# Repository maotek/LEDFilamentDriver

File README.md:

## LED Filament Driver

---

## Remarks

- KiCad project also contains a driver for EDP displays, however this schematic was not included in the final production PCB.
- Produced by JLCPCB.
- Crystal is not necessary for application not requiring precise timing.

---
## Issues

- Unfortunately, output 9 and 10 do not have PWM output. Will be fixed in the next revisions if any.
- AMS1117 3.3 is rated for 1A, make sure the LED filaments do no consume more than 1A. Otherwise they will overheat.
- For loads higher than 1A, consider buck converters.

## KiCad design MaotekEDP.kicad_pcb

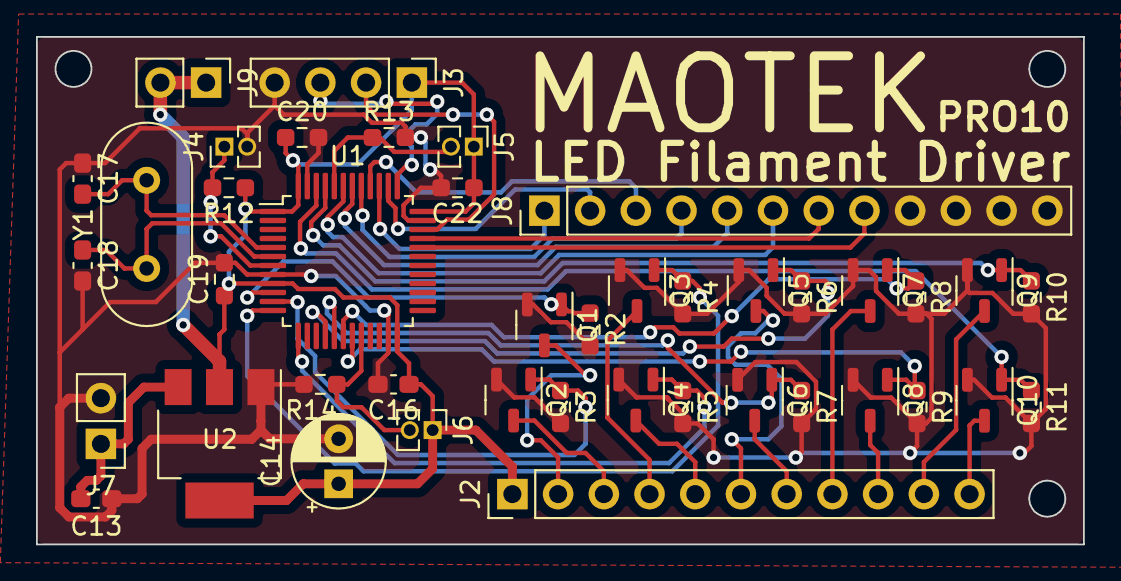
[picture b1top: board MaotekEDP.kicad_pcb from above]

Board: 2 copper layers, 58.2 x 28.2 mm, 42 parts (0 on the bottom side), 38 nets.

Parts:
C13, C16: 100nF; C_0603_1608Metric_Pad1.08x0.95mm_HandSolder
C14: 470uF; CP_Radial_D5.0mm_P2.50mm
C17, C18: 20p; C_0603_1608Metric_Pad1.08x0.95mm_HandSolder
C19, C20, C22: 100nF; R_0603_1608Metric_Pad0.98x0.95mm_HandSolder
J2: Conn_01x11; PinHeader_1x11_P2.54mm_Vertical
J3: Conn_01x04; PinHeader_1x04_P2.54mm_Vertical
J4, J5, J6: Conn_01x02; PinHeader_1x02_P1.27mm_Vertical
J7, J9: Conn_01x02; PinHeader_1x02_P2.54mm_Vertical
J8: Conn_01x12; PinHeader_1x12_P2.54mm_Vertical
Q1, Q2, Q3, Q4, Q5, Q6, Q7, Q8, Q9, Q10: Q_NMOS_GSD; SOT-23-3
R2, R3, R4, R5, R6, R7, R8, R9, R10, R11, R12, R13, R14: 10K; R_0603_1608Metric_Pad0.98x0.95mm_HandSolder
U1: STM32F103C8Tx; LQFP-48_7x7mm_P0.5mm
U2: AMS1117-3.3; SOT-223-3_TabPin2
Y1: 8MHz; Crystal_HC18-U_Vertical

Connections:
32: J8.8, U1.32 (PA11)
33: J8.7, U1.33 (PA12)
38: J8.2, U1.38 (PA15)
39: J8.1, U1.39 (PB3)
40: J8.3, U1.40 (PB4)
41: J8.4, U1.41 (PB5)
42: J8.5, U1.42 (PB6)
43: J8.6, U1.43 (PB7)
+3.3V: C14.1, C16.1, C19.1, C20.1, C22.1, J2.1, J3.1, J5.1, J6.1, J9.1, J9.2, R12.1, U1.1 (VBAT), U1.9 (VDDA), U1.24 (VDD), U1.36 (VDD), U1.48 (VDD), U2.2 (VO)
+5V: C13.1, J7.1, U2.3 (VI)
BOOT0: J5.2, R13.1, U1.44 (BOOT0)
BOOT1: J6.2, R14.1, U1.20 (PB2)
GND: C13.2, C14.2, C16.2, C17.1, C18.2, C19.2, C20.2, C22.2, J3.4, J4.2, J7.2, J8.9, J8.10, J8.11, J8.12, Q1.2 (S), Q2.2 (S), Q3.2 (S), Q4.2 (S), Q5.2 (S), Q6.2 (S), Q7.2 (S), Q8.2 (S), Q9.2 (S), Q10.2 (S), R2.2, R3.2, R4.2, R5.2, R6.2, R7.2, R8.2, R9.2, R10.2, R11.2, R13.2, R14.2, U1.8 (VSSA), U1.23 (VSS), U1.35 (VSS), U1.47 (VSS), U2.1 (GND)
NRST: J4.1, R12.2, U1.7 (NRST)
OSCIN: C17.2, U1.5 (PD0), Y1.2
OSCOUT: C18.1, U1.6 (PD1), Y1.1
SWCLK: J3.3, U1.37 (PA14)
SWIO: J3.2, U1.34 (PA13)
in1: Q1.1 (G), R2.1, U1.10 (PA0)
in2: Q2.1 (G), R3.1, U1.11 (PA1)
in3: Q3.1 (G), R4.1, U1.12 (PA2)
in4: Q4.1 (G), R5.1, U1.13 (PA3)
in5: Q5.1 (G), R6.1, U1.16 (PA6)
in6: Q6.1 (G), R7.1, U1.17 (PA7)
in7: Q7.1 (G), R8.1, U1.18 (PB0)
in8: Q8.1 (G), R9.1, U1.19 (PB1)
in9: Q9.1 (G), R10.1, U1.45 (PB8)
in10: Q10.1 (G), R11.1, U1.46 (PB9)
out1: J2.2, Q1.3 (D)
out2: J2.3, Q2.3 (D)
out3: J2.4, Q3.3 (D)
out4: J2.5, Q4.3 (D)
out5: J2.6, Q5.3 (D)
out6: J2.7, Q6.3 (D)
out7: J2.8, Q7.3 (D)
out8: J2.9, Q8.3 (D)
out9: J2.10, Q9.3 (D)
out10: J2.11, Q10.3 (D)

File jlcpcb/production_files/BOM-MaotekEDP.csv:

Comment,Designator,Footprint,LCSC
Q_NMOS_GSD,Q1,SOT-23-3,
Conn_01x02,J7,PinHeader_1x02_P2.54mm_Vertical,
8MHz,Y1,Crystal_HC18-U_Vertical,
AMS1117-3.3,U2,SOT-223-3_TabPin2,
STM32F103C8Tx,U1,LQFP-48_7x7mm_P0.5mm,
10K,R14,R_0603_1608Metric_Pad0.98x0.95mm_HandSolder,
10K,R13,R_0603_1608Metric_Pad0.98x0.95mm_HandSolder,
10K,R12,R_0603_1608Metric_Pad0.98x0.95mm_HandSolder,
10K,R11,R_0603_1608Metric_Pad0.98x0.95mm_HandSolder,
10K,R10,R_0603_1608Metric_Pad0.98x0.95mm_HandSolder,
10K,R9,R_0603_1608Metric_Pad0.98x0.95mm_HandSolder,
10K,R8,R_0603_1608Metric_Pad0.98x0.95mm_HandSolder,
10K,R7,R_0603_1608Metric_Pad0.98x0.95mm_HandSolder,
10K,R6,R_0603_1608Metric_Pad0.98x0.95mm_HandSolder,
10K,R5,R_0603_1608Metric_Pad0.98x0.95mm_HandSolder,
10K,R4,R_0603_1608Metric_Pad0.98x0.95mm_HandSolder,
10K,R3,R_0603_1608Metric_Pad0.98x0.95mm_HandSolder,
10K,R2,R_0603_1608Metric_Pad0.98x0.95mm_HandSolder,
Q_NMOS_GSD,Q10,SOT-23-3,
Q_NMOS_GSD,Q9,SOT-23-3,
Q_NMOS_GSD,Q8,SOT-23-3,
Q_NMOS_GSD,Q7,SOT-23-3,
Q_NMOS_GSD,Q6,SOT-23-3,
Q_NMOS_GSD,Q5,SOT-23-3,
Q_NMOS_GSD,Q4,SOT-23-3,
Q_NMOS_GSD,Q3,SOT-23-3,
Q_NMOS_GSD,Q2,SOT-23-3,
Conn_01x02,J6,PinHeader_1x02_P1.27mm_Vertical,
Conn_01x02,J5,PinHeader_1x02_P1.27mm_Vertical,
Conn_01x02,J4,PinHeader_1x02_P1.27mm_Vertical,
Conn_01x04,J3,PinHeader_1x04_P2.54mm_Vertical,
Conn_01x11,J2,PinHeader_1x11_P2.54mm_Vertical,
100nF,C22,R_0603_1608Metric_Pad0.98x0.95mm_HandSolder,
100nF,C20,R_0603_1608Metric_Pad0.98x0.95mm_HandSolder,
100nF,C19,R_0603_1608Metric_Pad0.98x0.95mm_HandSolder,
20p,C18,C_0603_1608Metric_Pad1.08x0.95mm_HandSolder,
20p,C17,C_0603_1608Metric_Pad1.08x0.95mm_HandSolder,
100nF,C16,C_0603_1608Metric_Pad1.08x0.95mm_HandSolder,
470uF,C14,CP_Radial_D5.0mm_P2.50mm,
100nF,C13,C_0603_1608Metric_Pad1.08x0.95mm_HandSolder,
Conn_01x02,J9,PinHeader_1x02_P2.54mm_Vertical,
Conn_01x12,J8,PinHeader_1x12_P2.54mm_Vertical,

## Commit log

2025-02-04 Add README
